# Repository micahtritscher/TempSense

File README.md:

# TempSense - ESP32-C3FH4 temperature logger Rev 0.1
*Micah Tritscher 07/25*

Wireless ESP32-C3FH4 based battery powered HDC1080DMBR temperature and humidty logger, with USB Type-C charging.

### Features
- I2C Texas Instruments HDC1080DMBR humidity and temperature sensor
- Impedance matched PCB antenna from TI AN043 application: https://www.ti.com/lit/an/swra117d/swra117d.pdf
- USB Type-C charging and programming
- BQ24074RGTR charging circuit (Designed for 500 mAh LiPO battery)
- Compact design at 25 mm x 50 mm

### Images
KiCAD 9.0 Renders

Manufactured by JLCPCB, assembled by hand

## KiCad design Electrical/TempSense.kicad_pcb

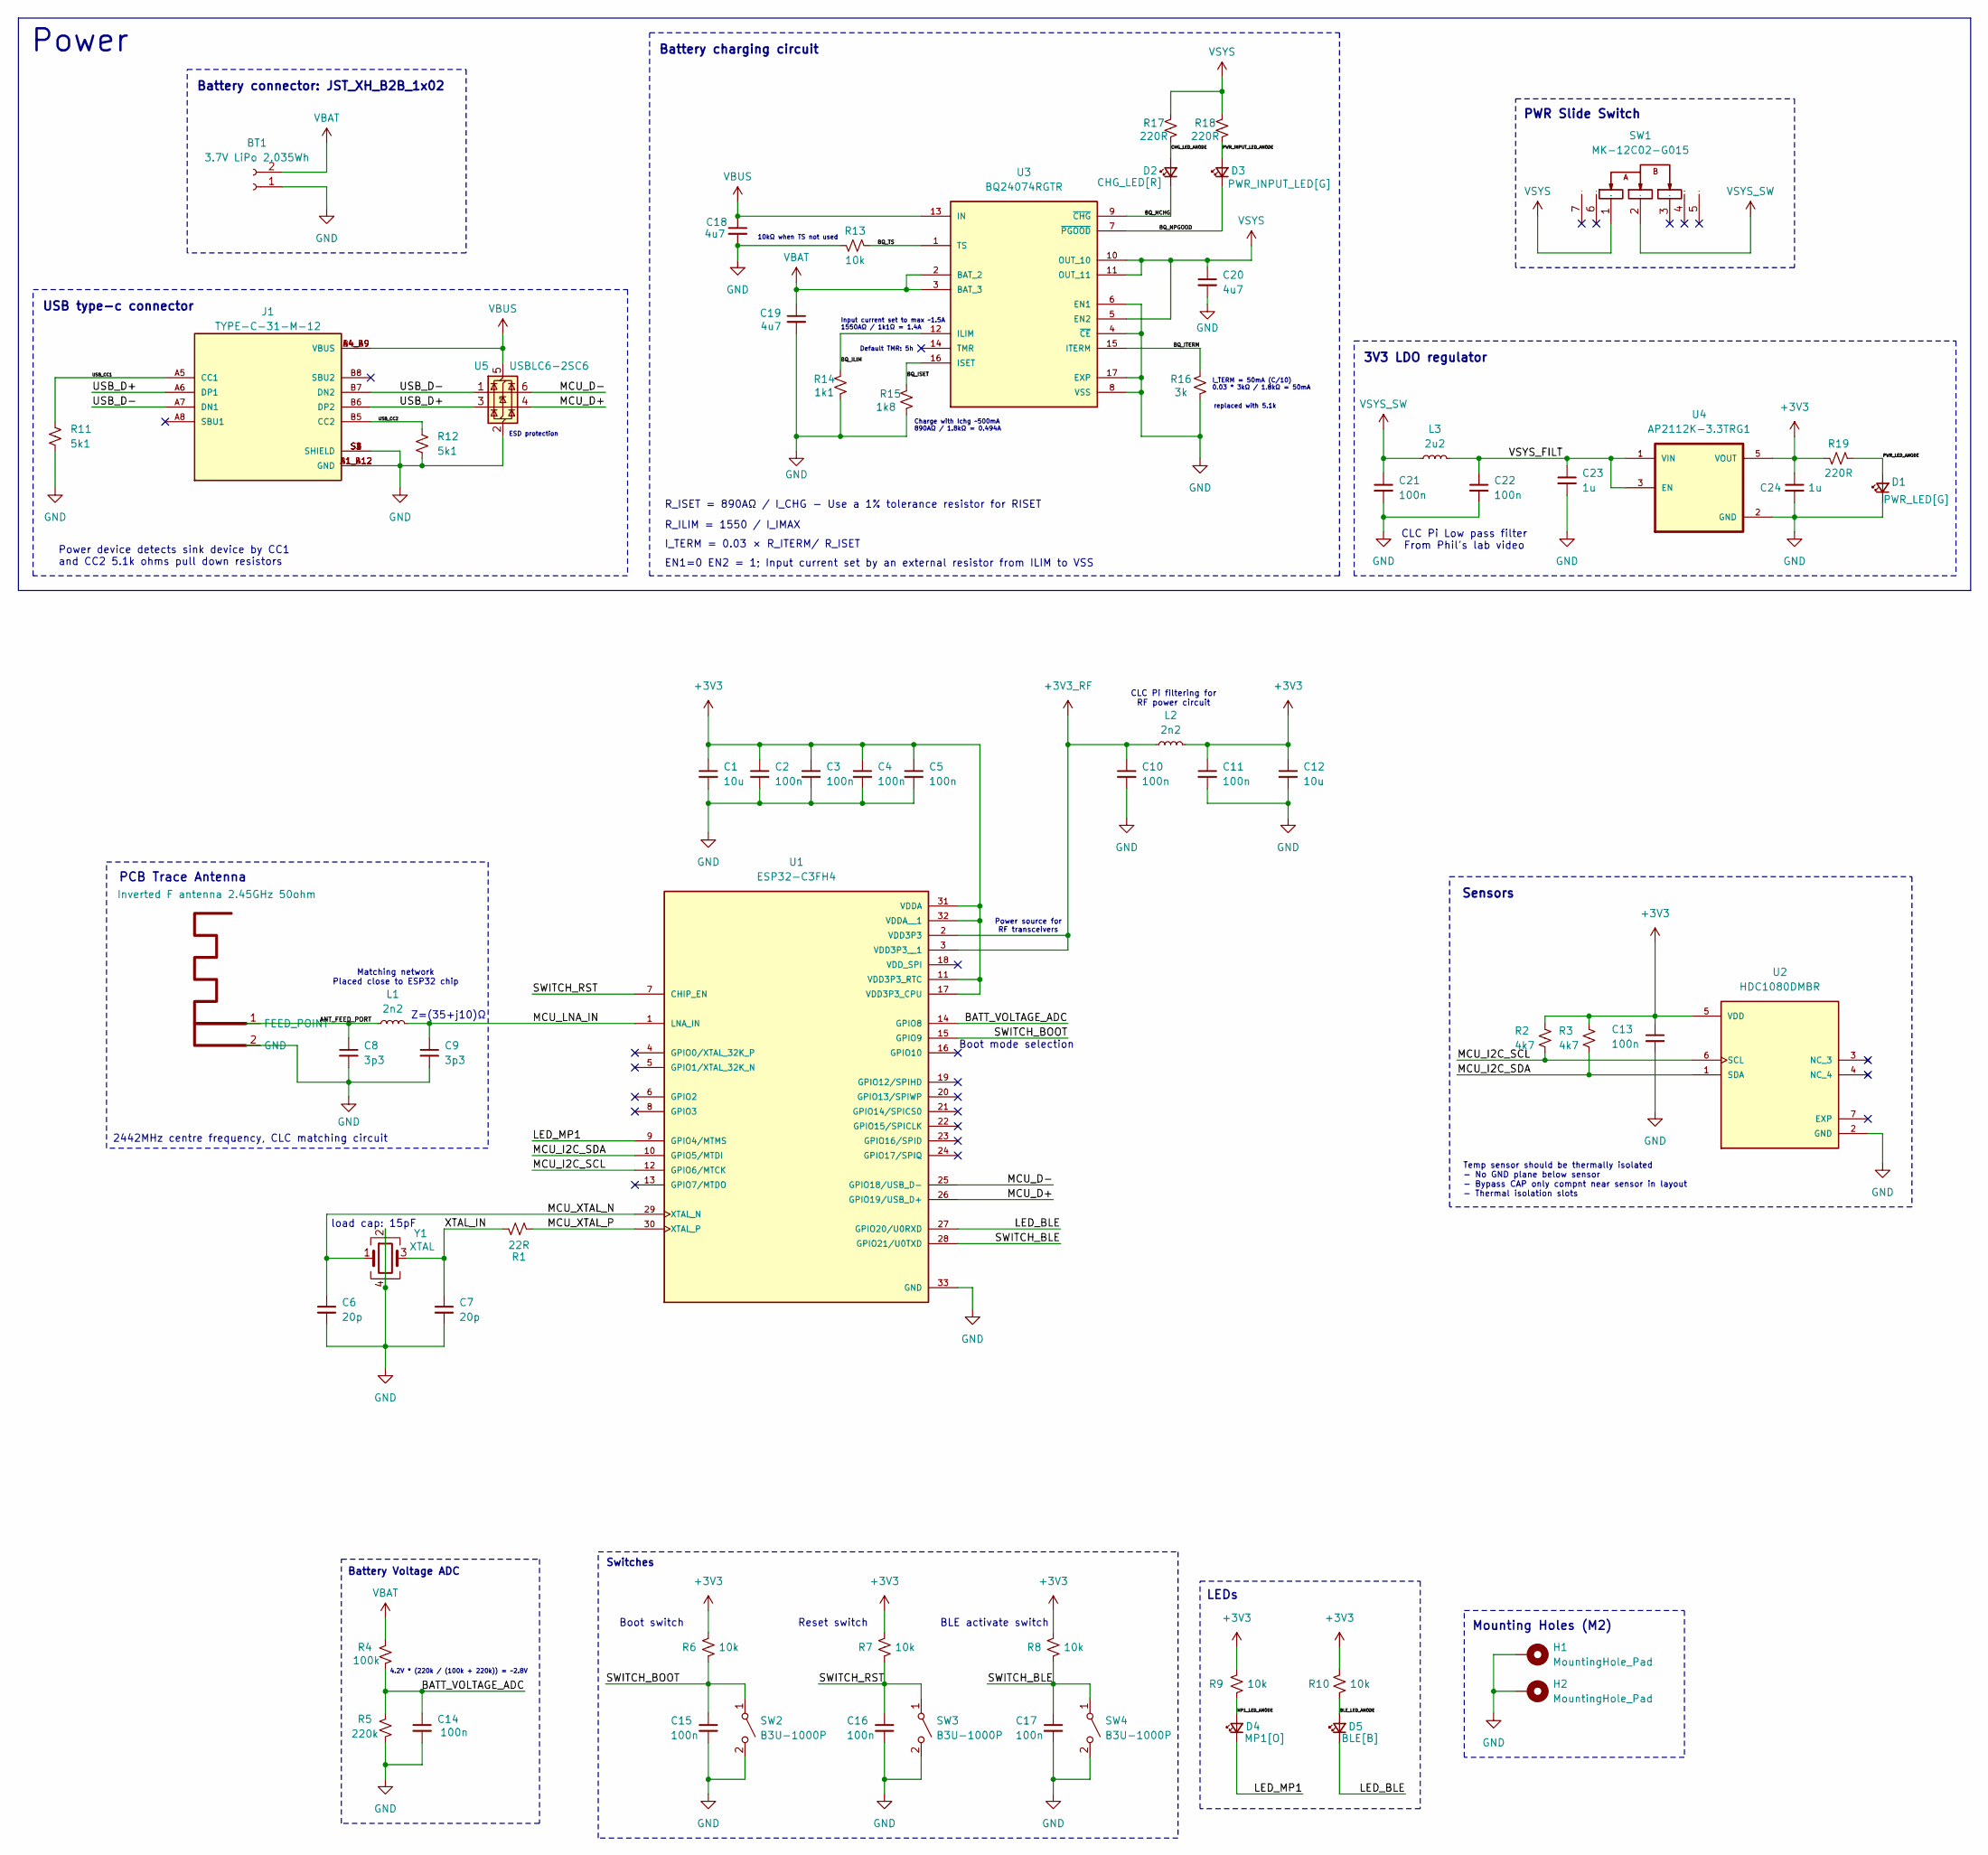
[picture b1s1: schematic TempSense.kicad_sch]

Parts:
ANT1: Inverted F antenna 2.45GHz 50ohm; Inverted_F_Meandered_Antenna_2.45GHz
BT1: 3.7V LiPo 2.035Wh; JST_XH_S2B-XH-A_1x02_P2.50mm_Horizontal
C1, C12: 10u; C_0603_1608Metric
C2, C3, C4, C5, C10, C11, C13, C14, C15, C16, C17, C21, C22: 100n; C_0402_1005Metric
C6, C7: 20p; C_0402_1005Metric
C8, C9: 3p3; C_0402_1005Metric
C18, C19, C20: 4u7; C_0603_1608Metric
C23, C24: 1u; C_0402_1005Metric
D1: PWR_LED[G]; LED_0603_1608Metric
D2: CHG_LED[R]; LED_0603_1608Metric
D3: PWR_INPUT_LED[G]; LED_0603_1608Metric
D4: MP1[O]; LED_0603_1608Metric
D5: BLE[B]; LED_0603_1608Metric
H1, H2: MountingHole_Pad; MountingHole_2.2mm_M2_DIN965_Pad
J1: TYPE-C-31-M-12; HRO_TYPE-C-31-M-12; PARTREV 2020.12.08
L1, L2: 2n2; L_0402_1005Metric
L3: 2u2; L_0402_1005Metric
R1: 22R; R_0402_1005Metric
R2, R3: 4k7; R_0402_1005Metric
R4: 100k; R_0402_1005Metric
R5: 220k; R_0402_1005Metric
R6, R7, R8, R9, R10, R13: 10k; R_0402_1005Metric
R11, R12: 5k1; R_0402_1005Metric
R14: 1k1; R_0402_1005Metric
R15: 1k8; R_0402_1005Metric
R16: 3k; R_0402_1005Metric
R17, R18, R19: 220R; R_0402_1005Metric
SW1: MK-12C02-G015; SW-SMD_G-SWITCH_MK-12C02-G015; Manufacturer Part MK-12C02-G015
SW2, SW3, SW4: B3U-1000P; SW_B3U-1000P
U1: ESP32-C3FH4; PARTREV 2.0
U2: HDC1080DMBR; PARTREV A
U3: BQ24074RGTR; PARTREV M
U4: AP2112K-3.3TRG1; PARTREV 2-2
U5: USBLC6-2SC6; SOT-23-6
Y1: XTAL; Crystal_SMD_3225-4Pin_3.2x2.5mm

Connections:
+3V3: C1.1, C2.1, C3.1, C4.1, C5.1, C11.1, C12.1, C13.1, C24.1, L2.2, R2.1, R3.1, R6.1, R7.1, R8.1, R9.1, R10.1, R19.2, U1.11 (VDD3P3_RTC), U1.17 (VDD3P3_CPU), U1.31 (VDDA), U1.32 (VDDA__1), U2.5 (VDD), U4.5 (VOUT)
+3V3_RF: C10.1, L2.1, U1.2 (VDD3P3), U1.3 (VDD3P3__1)
/ANT_FEED_PORT: ANT1.1 (FEED_POINT), C8.1, L1.1
/BATT_VOLTAGE_ADC: C14.1, R4.2, R5.1, U1.14 (GPIO8)
/BLE_LED_ANODE: D5.2 (A), R10.2
/BQ_ILIM: R14.2, U3.12 (ILIM)
/BQ_ISET: R15.2, U3.16 (ISET)
/BQ_ITERM: R16.2, U3.15 (ITERM)
/BQ_NCHG: D2.1 (K), U3.9 (~CHG)
/BQ_NPGOOD: D3.1 (K), U3.7 (~PGOOD)
/BQ_TS: R13.1, U3.1 (TS)
/CHG_LED_ANODE: D2.2 (A), R17.2
/LED_BLE: D5.1 (K), U1.27 (GPIO20/U0RXD)
/LED_MP1: D4.1 (K), U1.9 (GPIO4/MTMS)
/MCU_D+: U1.26 (GPIO19/USB_D+), U5.4 (I/O2)
/MCU_D-: U1.25 (GPIO18/USB_D-), U5.6 (I/O1)
/MCU_I2C_SCL: R2.2, U1.12 (GPIO6/MTCK), U2.6 (SCL)
/MCU_I2C_SDA: R3.2, U1.10 (GPIO5/MTDI), U2.1 (SDA)
/MCU_LNA_IN: C9.1, L1.2, U1.1 (LNA_IN)
/MCU_XTAL_N: C6.1, U1.29 (XTAL_N), Y1.1
/MCU_XTAL_P: R1.1, U1.30 (XTAL_P)
/MP1_LED_ANODE: D4.2 (A), R9.2
/PWR_INPUT_LED_ANODE: D3.2 (A), R18.2
/PWR_LED_ANODE: D1.2 (A), R19.1
/SWITCH_BLE: C17.1, R8.2, SW4.1 (A), U1.28 (GPIO21/U0TXD)
/SWITCH_BOOT: C15.1, R6.2, SW2.1 (A), U1.15 (GPIO9)
/SWITCH_RST: C16.1, R7.2, SW3.1 (A), U1.7 (CHIP_EN)
/USB_CC1: J1.A5 (CC1), R11.2
/USB_CC2: J1.B5 (CC2), R12.2
/USB_D+: J1.A6 (DP1), J1.B6 (DP2), U5.3 (I/O2)
/USB_D-: J1.A7 (DN1), J1.B7 (DN2), U5.1 (I/O1)
/VSYS_FILT: C22.1, C23.1, L3.2, U4.1 (VIN), U4.3 (EN)
/XTAL_IN: C7.1, R1.2, Y1.3
GND: ANT1.2 (GND), BT1.1, C1.2, C2.2, C3.2, C4.2, C5.2, C6.2, C7.2, C8.2, C9.2, C10.2, C11.2, C12.2, C13.2, C14.2, C15.2, C16.2, C17.2, C18.2, C19.2, C20.2, C21.2, C22.2, C23.2, C24.2, D1.1 (K), H1.1, H2.1, J1.A1_B12 (GND), J1.B1_A12 (GND), J1.S1 (SHIELD), J1.S2 (SHIELD), J1.S3 (SHIELD), J1.S4 (SHIELD), R5.2, R11.1, R12.1, R13.2, R14.1, R15.1, R16.1, SW2.2 (B), SW3.2 (B), SW4.2 (B), U1.33 (GND), U2.2 (GND), U3.4 (~CE), U3.6 (EN1), U3.8 (VSS), U3.17 (EXP), U4.2 (GND), U5.2 (GND), Y1.2, Y1.4; also elsewhere on the board
VBAT: BT1.2, C19.1, R4.1, U3.2 (BAT_2), U3.3 (BAT_3); also elsewhere on the board
VBUS: C18.1, J1.A4_B9 (VBUS), J1.B4_A9 (VBUS), U3.13 (IN), U5.5 (VBUS)
VSYS: C20.1, R17.1, R18.1, SW1.1, U3.5 (EN2), U3.10 (OUT_10), U3.11 (OUT_11)
VSYS_SW: C21.1, L3.1, SW1.2

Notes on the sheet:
load cap: 15pF
Charge with Ichg ~500mA 890AΩ / 1.8kΩ = 0.494A
PWR Slide Switch
Battery charging circuit
Z=(35+j10)Ω
R_ILIM = 1550 / I_IMAX
Mounting Holes (M2)
Power device detects sink device by CC1 and CC2 5.1k ohms pull down resistors
I_TERM = 50mA (C/10) 0.03 * 3kΩ / 1.8kΩ = 50mA
Battery Voltage ADC
Boot mode selection
Reset switch
Power source for RF transceivers
EN1=0 EN2 = 1; Input current set by an external resistor from ILIM to VSS
Input current set to max ~1.5A 1550AΩ / 1k1Ω = 1.4A
Sensors
BLE activate switch
CLC Pi filtering for RF power circuit
Matching network Placed close to ESP32 chip
I_TERM = 0.03 × R_ITERM/ R_ISET
R_ISET = 890AΩ / I_CHG
Boot switch
LEDs
ESD protection
CLC Pi Low pass filter From Phil's lab video
Switches
USB type-c connector
replaced with 5.1k
PCB Trace Antenna
Battery connector: JST_XH_B2B_1x02
4.2V * (220k / (100k + 220k)) = ~2.8V
Power
- Use a 1% tolerance resistor for RISET
Default TMR: 5h
10kΩ when TS not used
Temp sensor should be thermally isolated - No GND plane below sensor - Bypass CAP only compnt near sensor in layout - Thermal isolation slots
2442MHz centre frequency, CLC matching circuit
3V3 LDO regulator

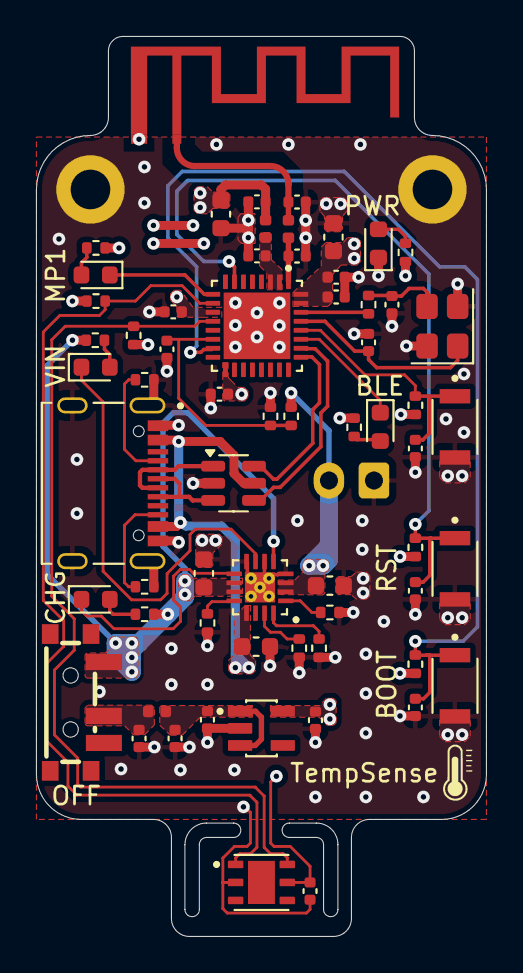
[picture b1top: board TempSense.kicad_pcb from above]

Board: 4 copper layers, 25.0 x 50.0 mm, 66 parts (1 on the bottom side), 38 nets.

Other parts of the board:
BAT: 3.7V LiPo 2.035Wh; JST_XH_S2B-XH-A_1x02_P2.50mm_Horizontal

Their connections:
GND: BAT.1; also elsewhere on the board
VBAT: BAT.2; also elsewhere on the board

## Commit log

2025-08-23 Uploaded PCB renders and photos
2025-08-23 Rename IMG_20250731_190445.jpg to Images/IMG_20250731_190445.jpg
2025-08-23 Rename IMG_20250731_190445.jpg to TempSenseAssembled.jpg
2025-08-23 Rename TempSensePCB.png to Images/RenderTempSensePCB.png
2025-08-23 Rename TempSensePCBBottom.png to Images/RenderTempSensePCBBottom.png
2025-08-23 Rename TempSensePCBTop.png to Images/RenderTempSensePCBTop.png
2025-08-23 Added images in README
2025-08-23 Added KiCAD project folder
2025-08-24 Added firmware folder
2025-08-24 Added manufacturing folder
